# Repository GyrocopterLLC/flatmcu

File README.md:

# flatmcu
Hardware design for the flatmcu - an STM32G4 based BLDC / FOC motor controller.

## Features
All schematic and layout was created with KiCad EDA (https://kicad.org).

The controller is based on the STM32G473CB microcontroller from ST Microelectronics. It contains an ARM Cortex-M4 core at up to 170MHz. The three-phase bridge driver is the TI DRV8353RS, which also contains shunt resistor current sensors and a 95V buck regulator.

The MOSFETs in the three-phase bridge (Toshiba TPW4R50ANH) are dual-side cooling. There's a large metal pad on top of them. A heatsink should be attached there. The opposite side of the board is intended for soldering on the large battery and phase wires.

## Schematic
### Main

### Microcontroller

### Three-phase bridge

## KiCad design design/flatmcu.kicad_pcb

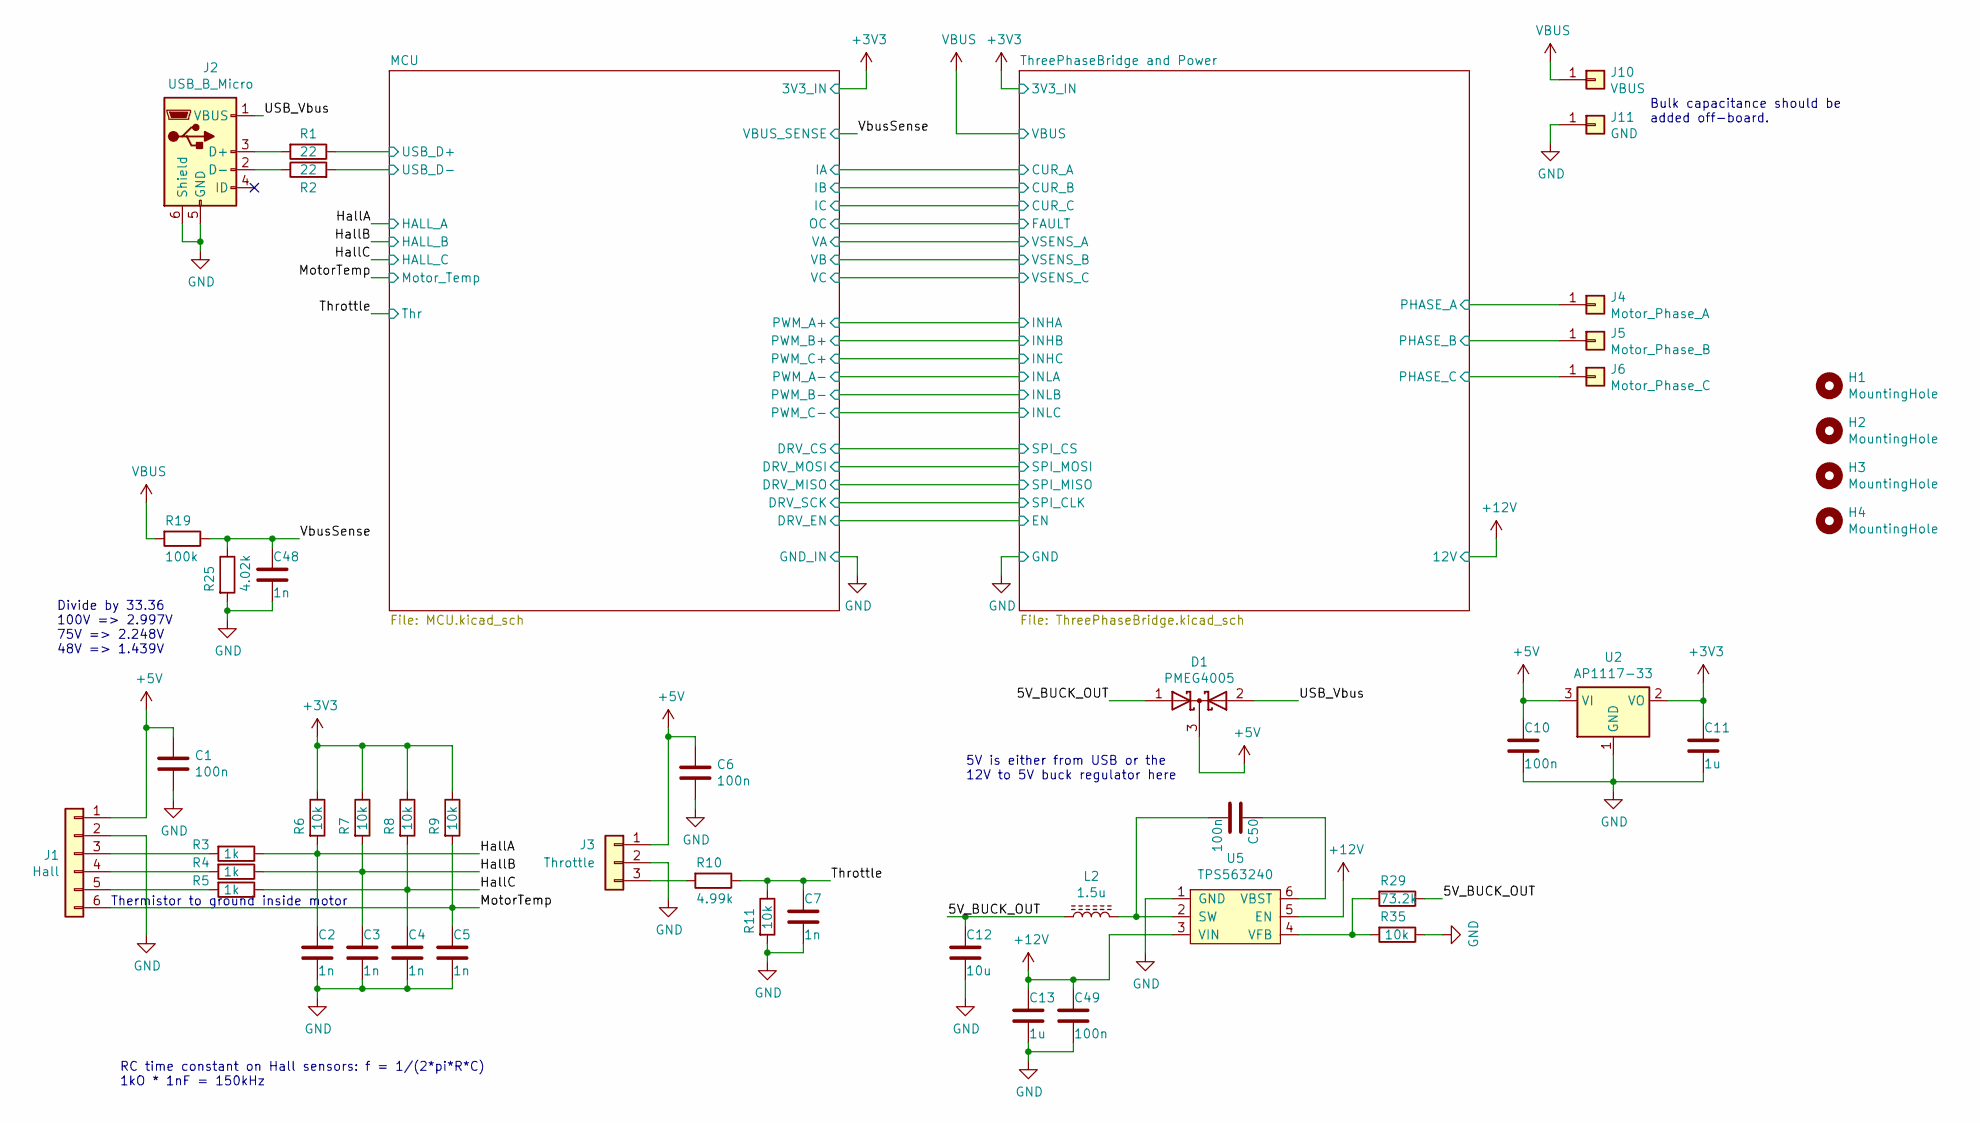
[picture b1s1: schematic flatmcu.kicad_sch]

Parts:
C1, C6, C10: 100n; C_0603_1608Metric; Voltage 6.3V
C2, C3, C4, C5, C7, C48: 1n; C_0603_1608Metric; Voltage 6.3V
C11: 1u; C_0603_1608Metric; Voltage 6.3V
C12: 10u; C_0603_1608Metric; Voltage 6.3V
C13: 1u; C_0603_1608Metric; Voltage 16V
C49, C50: 100n; C_0603_1608Metric; Voltage 16V
D1: PMEG4005; SOT-23
H1, H2, H3, H4: MountingHole; MountingHole_3.2mm_M3
J1: Hall; JST_XH_B6B-XH-A_1x06_P2.50mm_Vertical
J2: USB_B_Micro; USB_Micro_B_Female_10118193-0001LF
J3: Throttle; JST_XH_B3B-XH-A_1x03_P2.50mm_Vertical
J4: Motor_Phase_A; SolderWirePad_1x01_SMD_5x10mm
J5: Motor_Phase_B; SolderWirePad_1x01_SMD_5x10mm
J6: Motor_Phase_C; SolderWirePad_1x01_SMD_5x10mm
J10: VBUS; SolderWirePad_1x01_SMD_5x10mm
J11: GND; SolderWirePad_1x01_SMD_5x10mm
L2: 1.5u; Bourns_SRN3015
R1, R2: 22; R_0603_1608Metric
R3, R4, R5: 1k; R_0603_1608Metric
R6, R7, R8, R9, R11, R35: 10k; R_0603_1608Metric
R10: 4.99k; R_0603_1608Metric
R19: 100k; R_0603_1608Metric
R25: 4.02k; R_0603_1608Metric
R29: 73.2k; R_0603_1608Metric
U2: AP1117-33; SOT-223-3_TabPin2
U5: TPS563240; SOT-23-6

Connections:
+3V3: C11.1, R6.1, R7.1, R8.1, R9.1, U2.2 (VO); also elsewhere on the board
+5V: C1.1, C6.1, C10.1, D1.3 (K), J1.1, J3.1, U2.3 (VI)
+12V: C13.1, C49.1, U5.3 (VIN), U5.5 (EN); also elsewhere on the board
/5V_BUCK_OUT: C12.1, D1.1 (A), L2.1, R29.1
/HallA: C2.1, R3.1, R6.2; also elsewhere on the board
/HallB: C3.1, R4.1, R7.2; also elsewhere on the board
/HallC: C4.1, R5.1, R8.2; also elsewhere on the board
/MCU/USB_D+: R1.1; also elsewhere on the board
/MCU/USB_D-: R2.2; also elsewhere on the board
/MotorTemp: C5.1, J1.6, R9.2; also elsewhere on the board
/ThreePhaseBridge and Power/PHASE_A: J4.1; also elsewhere on the board
/ThreePhaseBridge and Power/PHASE_B: J5.1; also elsewhere on the board
/ThreePhaseBridge and Power/PHASE_C: J6.1; also elsewhere on the board
/Throttle: C7.1, R10.1, R11.1; also elsewhere on the board
/USB_Vbus: D1.2 (A), J2.1 (VBUS)
/VbusSense: C48.1, R19.1, R25.1; also elsewhere on the board
GND: C1.2, C2.2, C3.2, C4.2, C5.2, C6.2, C7.2, C10.2, C11.2, C12.2, C13.2, C48.2, C49.2, J1.2, J2.5 (GND), J2.6 (Shield), J3.2, J11.1, R11.2, R25.2, R35.1, U2.1 (GND), U5.1 (GND); also elsewhere on the board
unnamed: C50.1, U5.6 (VBST)
unnamed: C50.2, L2.2, U5.2 (SW)
unnamed: J1.3, R3.2
unnamed: J1.4, R4.2
unnamed: J1.5, R5.2
unnamed: J2.2 (D-), R2.1
unnamed: J2.3 (D+), R1.2
unnamed: J3.3, R10.2
unnamed: R29.2, R35.2, U5.4 (VFB)
VBUS: J10.1, R19.2; also elsewhere on the board

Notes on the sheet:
RC time constant on Hall sensors: f = 1/(2*pi*R*C) 1kO * 1nF = 150kHz
Divide by 33.36 100V => 2.997V 75V => 2.248V 48V => 1.439V
Thermistor to ground inside motor
Bulk capacitance should be added off-board.
5V is either from USB or the 12V to 5V buck regulator here

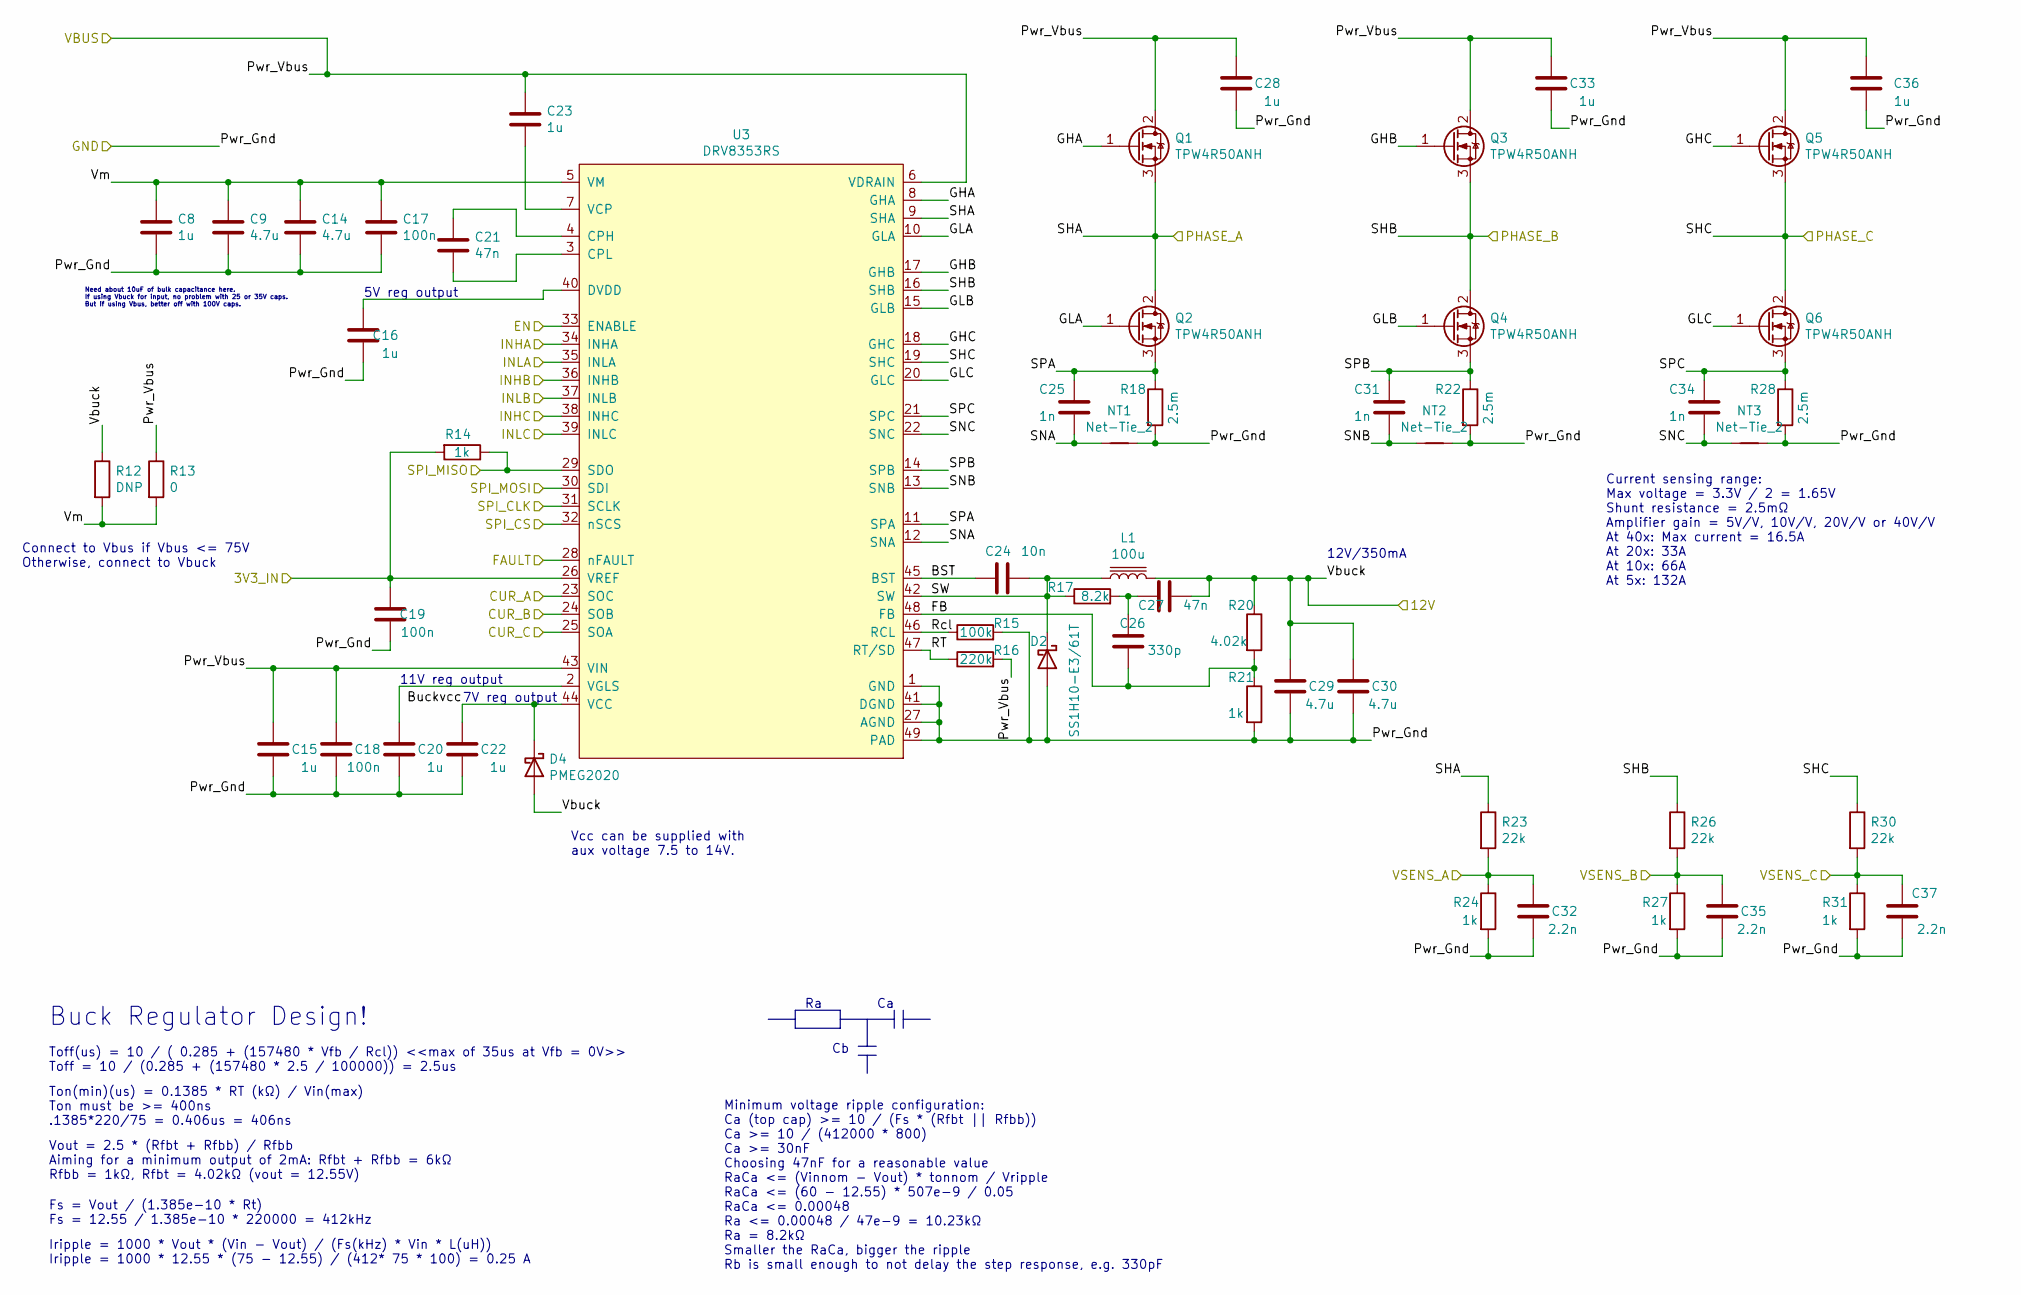
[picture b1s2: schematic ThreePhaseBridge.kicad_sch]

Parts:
C8: 1u; C_1210_3225Metric; Voltage 100V
C9, C14: 4.7u; C_1210_3225Metric; Voltage 100V
C15, C28, C33, C36: 1u; C_1206_3216Metric; Voltage 100V
C16: 1u; C_0603_1608Metric; Voltage 6.3V
C17, C18: 100n; C_0805_2012Metric; Voltage 100V
C19: 100n; C_0603_1608Metric; Voltage 6.3V
C20, C22, C23: 1u; C_0603_1608Metric; Voltage 16V
C21: 47n; C_0805_2012Metric; Voltage 100V
C24: 10n; C_0603_1608Metric; Voltage 16V
C25, C31, C34: 1n; C_0603_1608Metric
C26: 330p; C_0603_1608Metric; Voltage 16V
C27: 47n; C_0603_1608Metric; Voltage 16V
C29, C30: 4.7u; C_0805_2012Metric; Voltage 16V
C32, C35, C37: 2.2n; C_0603_1608Metric; Voltage 16V
D2: SS1H10-E3/61T; D_SMA
D4: PMEG2020; D_SOD-323F
L1: 100u; NR6045
NT1, NT2, NT3: Net-Tie_2; NetTie-2_SMD_Pad0.5mm
Q1, Q2, Q3, Q4, Q5, Q6: TPW4R50ANH; Toshiba_DSOP-Advance
R12: DNP; R_0603_1608Metric
R13: 0; R_0603_1608Metric
R14, R21, R24, R27, R31: 1k; R_0603_1608Metric
R15: 100k; R_0603_1608Metric
R16: 220k; R_0603_1608Metric
R17: 8.2k; R_0603_1608Metric
R18, R22, R28: 2.5m; R_2512_6332Metric
R20: 4.02k; R_0603_1608Metric
R23, R26, R30: 22k; R_0603_1608Metric
U3: DRV8353RS; TI-RGZ-48-QFN

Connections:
+3V3: C19.2, R14.2, U3.26 (VREF); also elsewhere on the board
+12V: C27.1, C29.2, C30.2, D4.2 (A), L1.2, R12.1, R20.1; also elsewhere on the board
/MCU/DRV_CS: U3.32 (nSCS); also elsewhere on the board
/MCU/DRV_EN: U3.33 (ENABLE); also elsewhere on the board
/MCU/DRV_MISO: R14.1, U3.29 (SDO); also elsewhere on the board
/MCU/DRV_MOSI: U3.30 (SDI); also elsewhere on the board
/MCU/DRV_SCK: U3.31 (SCLK); also elsewhere on the board
/MCU/VA: C32.2, R23.2, R24.1; also elsewhere on the board
/MCU/VB: C35.2, R26.2, R27.1; also elsewhere on the board
/MCU/VC: C37.2, R30.2, R31.1; also elsewhere on the board
/ThreePhaseBridge and Power/BST: C24.2, U3.45 (BST)
/ThreePhaseBridge and Power/Buckvcc: C22.2, D4.1 (K), U3.44 (VCC)
/ThreePhaseBridge and Power/CUR_A: U3.23 (SOC); also elsewhere on the board
/ThreePhaseBridge and Power/CUR_B: U3.24 (SOB); also elsewhere on the board
/ThreePhaseBridge and Power/CUR_C: U3.25 (SOA); also elsewhere on the board
/ThreePhaseBridge and Power/FAULT: U3.28 (nFAULT); also elsewhere on the board
/ThreePhaseBridge and Power/FB: C26.1, R20.2, R21.1, U3.48 (FB)
/ThreePhaseBridge and Power/GHA: Q1.1 (G), U3.8 (GHA)
/ThreePhaseBridge and Power/GHB: Q3.1 (G), U3.17 (GHB)
/ThreePhaseBridge and Power/GHC: Q5.1 (G), U3.18 (GHC)
/ThreePhaseBridge and Power/GLA: Q2.1 (G), U3.10 (GLA)
/ThreePhaseBridge and Power/GLB: Q4.1 (G), U3.15 (GLB)
/ThreePhaseBridge and Power/GLC: Q6.1 (G), U3.20 (GLC)
/ThreePhaseBridge and Power/INHA: U3.34 (INHA); also elsewhere on the board
/ThreePhaseBridge and Power/INHB: U3.36 (INHB); also elsewhere on the board
/ThreePhaseBridge and Power/INHC: U3.38 (INHC); also elsewhere on the board
/ThreePhaseBridge and Power/INLA: U3.35 (INLA); also elsewhere on the board
/ThreePhaseBridge and Power/INLB: U3.37 (INLB); also elsewhere on the board
/ThreePhaseBridge and Power/INLC: U3.39 (INLC); also elsewhere on the board
/ThreePhaseBridge and Power/PHASE_A: Q1.3 (S), Q2.2 (D), R23.1, U3.9 (SHA); also elsewhere on the board
/ThreePhaseBridge and Power/PHASE_B: Q3.3 (S), Q4.2 (D), R26.1, U3.16 (SHB); also elsewhere on the board
/ThreePhaseBridge and Power/PHASE_C: Q5.3 (S), Q6.2 (D), R30.1, U3.19 (SHC); also elsewhere on the board
/ThreePhaseBridge and Power/RT: R16.1, U3.47 (RT/SD)
/ThreePhaseBridge and Power/Rcl: R15.1, U3.46 (RCL)
/ThreePhaseBridge and Power/SNA: C25.1, NT1.1, U3.12 (SNA)
/ThreePhaseBridge and Power/SNB: C31.1, NT2.1, U3.13 (SNB)
/ThreePhaseBridge and Power/SNC: C34.1, NT3.1, U3.22 (SNC)
/ThreePhaseBridge and Power/SPA: C25.2, Q2.3 (S), R18.1, U3.11 (SPA)
/ThreePhaseBridge and Power/SPB: C31.2, Q4.3 (S), R22.1, U3.14 (SPB)
/ThreePhaseBridge and Power/SPC: C34.2, Q6.3 (S), R28.1, U3.21 (SPC)
/ThreePhaseBridge and Power/SW: C24.1, D2.1 (K), L1.1, R17.1, U3.42 (SW)
/ThreePhaseBridge and Power/Vm: C8.1, C9.1, C14.1, C17.1, R12.2, R13.2, U3.5 (VM)
GND: C8.2, C9.2, C14.2, C15.1, C16.1, C17.2, C18.1, C19.1, C20.1, C22.1, C28.1, C29.1, C30.1, C32.1, C33.1, C35.1, C36.1, C37.1, D2.2 (A), NT1.2, NT2.2, NT3.2, R15.2, R18.2, R21.2, R22.2, R24.2, R27.2, R28.2, R31.2, U3.1 (GND), U3.27 (AGND), U3.41 (DGND), U3.49 (PAD); also elsewhere on the board
unnamed: C16.2, U3.40 (DVDD)
unnamed: C20.2, U3.2 (VGLS)
unnamed: C21.1, U3.4 (CPH)
unnamed: C21.2, U3.3 (CPL)
unnamed: C23.2, U3.7 (VCP)
unnamed: C26.2, C27.2, R17.2
VBUS: C15.2, C18.2, C23.1, C28.2, C33.2, C36.2, Q1.2 (D), Q3.2 (D), Q5.2 (D), R13.1, R16.2, U3.6 (VDRAIN), U3.43 (VIN); also elsewhere on the board

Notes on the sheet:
Buck Regulator Design!
Current sensing range: Max voltage = 3.3V / 2 = 1.65V Shunt resistance = 2.5mΩ Amplifier gain = 5V/V, 10V/V, 20V/V or 40V/V At 40x: Max current = 16.5A At 20x: 33A At 10x: 66A At 5x: 132A
Vout = 2.5 * (Rfbt + Rfbb) / Rfbb Aiming for a minimum output of 2mA: Rfbt + Rfbb = 6kΩ Rfbb = 1kΩ, Rfbt = 4.02kΩ (vout = 12.55V)
5V reg output
Vcc can be supplied with aux voltage 7.5 to 14V.
Minimum voltage ripple configuration: Ca (top cap) >= 10 / (Fs * (Rfbt || Rfbb)) Ca >= 10 / (412000 * 800) Ca >= 30nF Choosing 47nF for a reasonable value RaCa <= (Vinnom - Vout) * tonnom / Vripple RaCa <= (60 - 12.55) * 507e-9 / 0.05 RaCa <= 0.00048 Ra <= 0.00048 / 47e-9 = 10.23kΩ Ra = 8.2kΩ Small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
12V/350mA
11V reg output
Iripple = 1000 * Vout * (Vin - Vout) / (Fs(kHz) * Vin * L(uH)) Iripple = 1000 * 12.55 * (75 - 12.55) / (412* 75 * 100) = 0.25 A
Ton(min)(us) = 0.1385‬ * RT (kΩ) / Vin(max) Ton must be >= 400ns .1385*220/75 = 0.406us = 406ns
7V reg output
Connect to Vbus if Vbus <= 75V Otherwise, connect to Vbuck
Fs = Vout / (1.385e-10 * Rt) Fs = 12.55 / 1.385e-10 * 220000 = 412kHz
Toff(us) = 10 / ( 0.285 + (157480 * Vfb / Rcl)) <<max of 35us at Vfb = 0V>> Toff = 10 / (0.285 + (157480 * 2.5 / 100000)) = 2.5us
Need about 10uF of bulk capacitance here. If using Vbuck for input, no problem with 25 or 35V caps. But if using Vbus, better off with 100V caps.

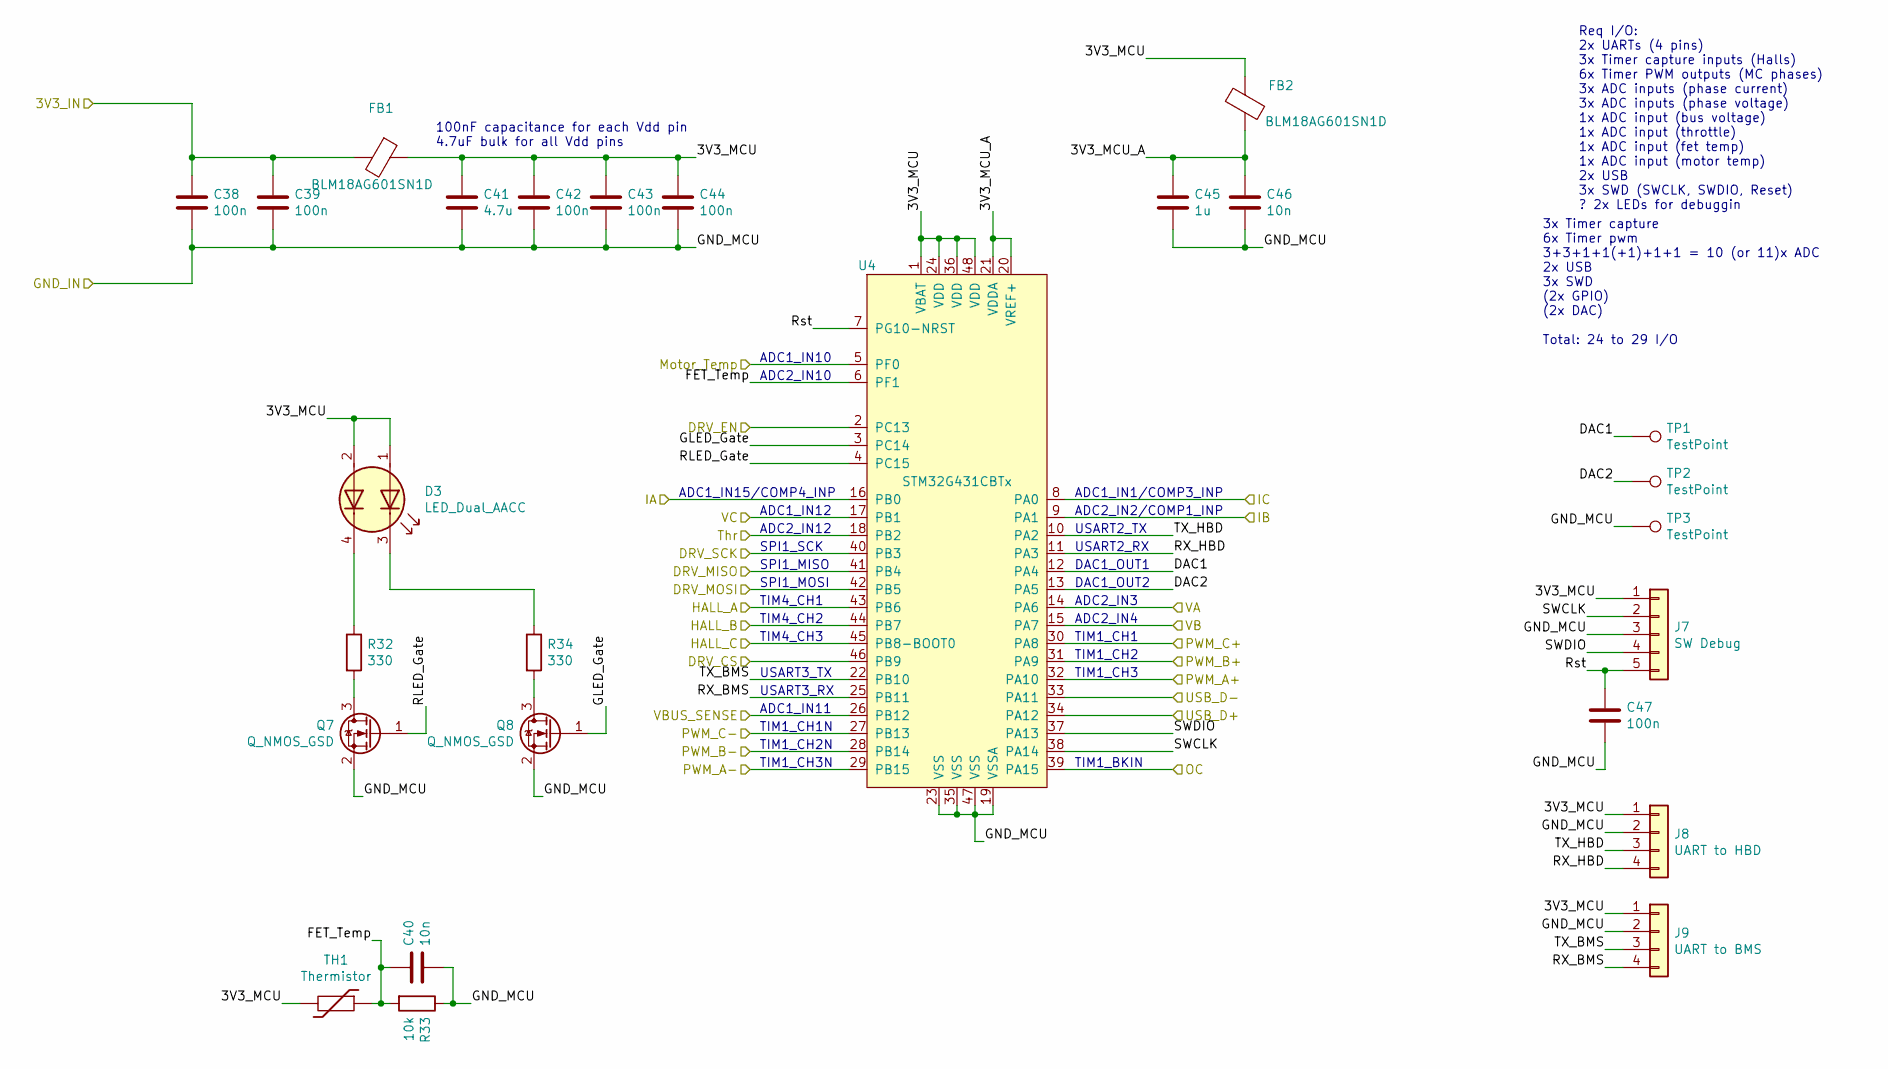
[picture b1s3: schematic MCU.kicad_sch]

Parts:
C38, C39, C42, C43, C44, C47: 100n; C_0603_1608Metric
C40, C46: 10n; C_0603_1608Metric
C41: 4.7u; C_0603_1608Metric
C45: 1u; C_0603_1608Metric
D3: LED_Dual_AACC; LED_RGB_1210
FB1, FB2: BLM18AG601SN1D; R_0603_1608Metric
J7: SW Debug; JST_SH_SM05B-SRSS-TB_1x05-1MP_P1.00mm_Horizontal
J8: UART to HBD; JST_XH_B4B-XH-A_1x04_P2.50mm_Vertical
J9: UART to BMS; JST_XH_B4B-XH-A_1x04_P2.50mm_Vertical
Q7, Q8: Q_NMOS_GSD; SOT-23
R32, R34: 330; R_0603_1608Metric
R33: 10k; R_0603_1608Metric
TH1: Thermistor; R_0603_1608Metric
TP1, TP2, TP3: TestPoint; PinHeader_1x01_P1.00mm_Vertical
U4: STM32G431CBTx; LQFP-48_7x7mm_P0.5mm

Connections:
+3V3: C38.1, C39.1, FB1.2; also elsewhere on the board
/HallA: U4.43 (PB6); also elsewhere on the board
/HallB: U4.44 (PB7); also elsewhere on the board
/HallC: U4.45 (PB8-BOOT0); also elsewhere on the board
/MCU/3V3_MCU: C41.1, C42.1, C43.1, C44.1, D3.1 (A1), D3.2 (A2), FB1.1, FB2.2, J7.1, J8.1, J9.1, TH1.2, U4.1 (VBAT), U4.24 (VDD), U4.36 (VDD), U4.48 (VDD)
/MCU/3V3_MCU_A: C45.1, C46.1, FB2.1, U4.20 (VREF+), U4.21 (VDDA)
/MCU/DAC1: TP1.1, U4.12 (PA4)
/MCU/DAC2: TP2.1, U4.13 (PA5)
/MCU/DRV_CS: U4.46 (PB9); also elsewhere on the board
/MCU/DRV_EN: U4.2 (PC13); also elsewhere on the board
/MCU/DRV_MISO: U4.41 (PB4); also elsewhere on the board
/MCU/DRV_MOSI: U4.42 (PB5); also elsewhere on the board
/MCU/DRV_SCK: U4.40 (PB3); also elsewhere on the board
/MCU/FET_Temp: C40.1, R33.2, TH1.1, U4.6 (PF1)
/MCU/GLED_Gate: Q8.1 (G), U4.3 (PC14)
/MCU/RLED_Gate: Q7.1 (G), U4.4 (PC15)
/MCU/RX_BMS: J9.4, U4.25 (PB11)
/MCU/RX_HBD: J8.4, U4.11 (PA3)
/MCU/Rst: C47.1, J7.5, U4.7 (PG10-NRST)
/MCU/SWCLK: J7.2, U4.38 (PA14)
/MCU/SWDIO: J7.4, U4.37 (PA13)
/MCU/TX_BMS: J9.3, U4.22 (PB10)
/MCU/TX_HBD: J8.3, U4.10 (PA2)
/MCU/USB_D+: U4.34 (PA12); also elsewhere on the board
/MCU/USB_D-: U4.33 (PA11); also elsewhere on the board
/MCU/VA: U4.14 (PA6); also elsewhere on the board
/MCU/VB: U4.15 (PA7); also elsewhere on the board
/MCU/VC: U4.17 (PB1); also elsewhere on the board
/MotorTemp: U4.5 (PF0); also elsewhere on the board
/ThreePhaseBridge and Power/CUR_A: U4.16 (PB0); also elsewhere on the board
/ThreePhaseBridge and Power/CUR_B: U4.9 (PA1); also elsewhere on the board
/ThreePhaseBridge and Power/CUR_C: U4.8 (PA0); also elsewhere on the board
/ThreePhaseBridge and Power/FAULT: U4.39 (PA15); also elsewhere on the board
/ThreePhaseBridge and Power/INHA: U4.32 (PA10); also elsewhere on the board
/ThreePhaseBridge and Power/INHB: U4.31 (PA9); also elsewhere on the board
/ThreePhaseBridge and Power/INHC: U4.30 (PA8); also elsewhere on the board
/ThreePhaseBridge and Power/INLA: U4.29 (PB15); also elsewhere on the board
/ThreePhaseBridge and Power/INLB: U4.28 (PB14); also elsewhere on the board
/ThreePhaseBridge and Power/INLC: U4.27 (PB13); also elsewhere on the board
/Throttle: U4.18 (PB2); also elsewhere on the board
/VbusSense: U4.26 (PB12); also elsewhere on the board
GND: C38.2, C39.2, C40.2, C41.2, C42.2, C43.2, C44.2, C45.2, C46.2, C47.2, J7.3, J8.2, J9.2, Q7.2 (S), Q8.2 (S), R33.1, TP3.1, U4.19 (VSSA), U4.23 (VSS), U4.35 (VSS), U4.47 (VSS); also elsewhere on the board
unnamed: D3.3 (K1), R34.1
unnamed: D3.4 (K2), R32.1
unnamed: Q7.3 (D), R32.2
unnamed: Q8.3 (D), R34.2

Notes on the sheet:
ADC1_IN11
TIM1_CH3N
Req I/O: 2x UARTs (4 pins) 3x Timer capture inputs (Halls) 6x Timer PWM outputs (MC phases) 3x ADC inputs (phase current) 3x ADC inputs (phase voltage) 1x ADC input (bus voltage) 1x ADC input (throttle) 1x ADC input (fet temp) 1x ADC input (motor temp) 2x USB 3x SWD (SWCLK, SWDIO, Reset) ? 2x LEDs 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
DAC1_OUT2
TIM4_CH2
USART3_RX
SPI1_MOSI
ADC1_IN10
DAC1_OUT1
ADC2_IN3
ADC2_IN4
TIM1_CH2
SPI1_SCK
TIM1_CH2N
ADC2_IN12
ADC1_IN1/COMP3_INP
TIM4_CH3
100nF capacitance for each Vdd pin 4.7uF bulk for all Vdd pins
USART2_TX
ADC1_IN15/COMP4_INP
TIM4_CH1
TIM1_CH3
USART3_TX
ADC1_IN12
TIM1_CH1N
3x Timer capture 6x Timer pwm 3+3+1+1(+1)+1+1 = 10 (or 11)x ADC 2x USB 3x SWD (2x GPIO) (2x DAC) Total: 24 to 29 I/O
ADC2_IN2/COMP1_INP
TIM1_CH1
USART2_RX
SPI1_MISO
TIM1_BKIN
ADC2_IN10

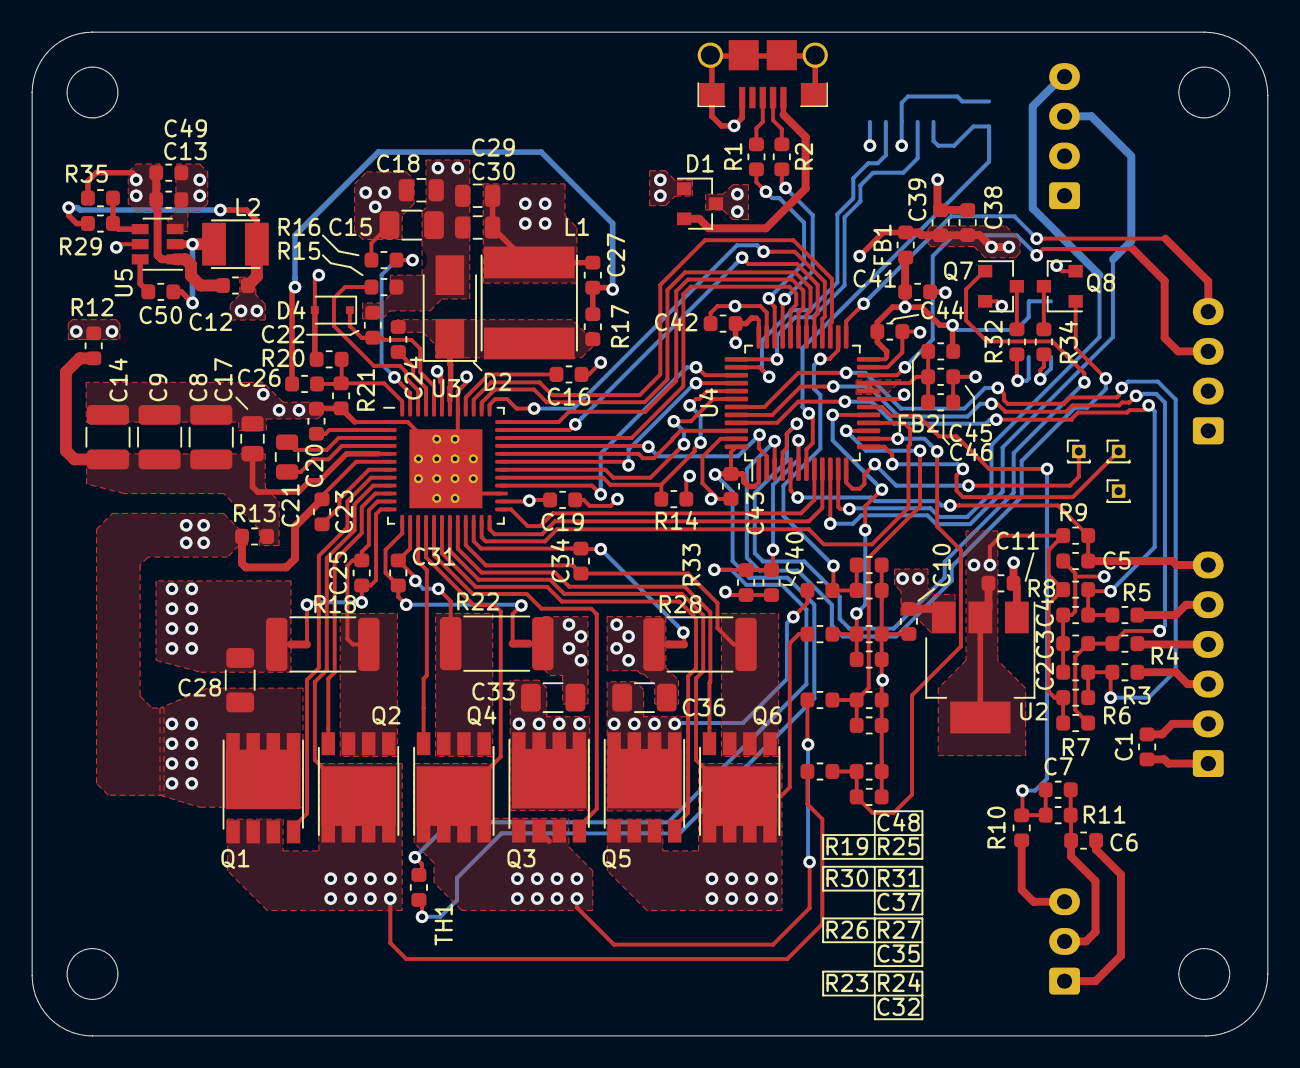
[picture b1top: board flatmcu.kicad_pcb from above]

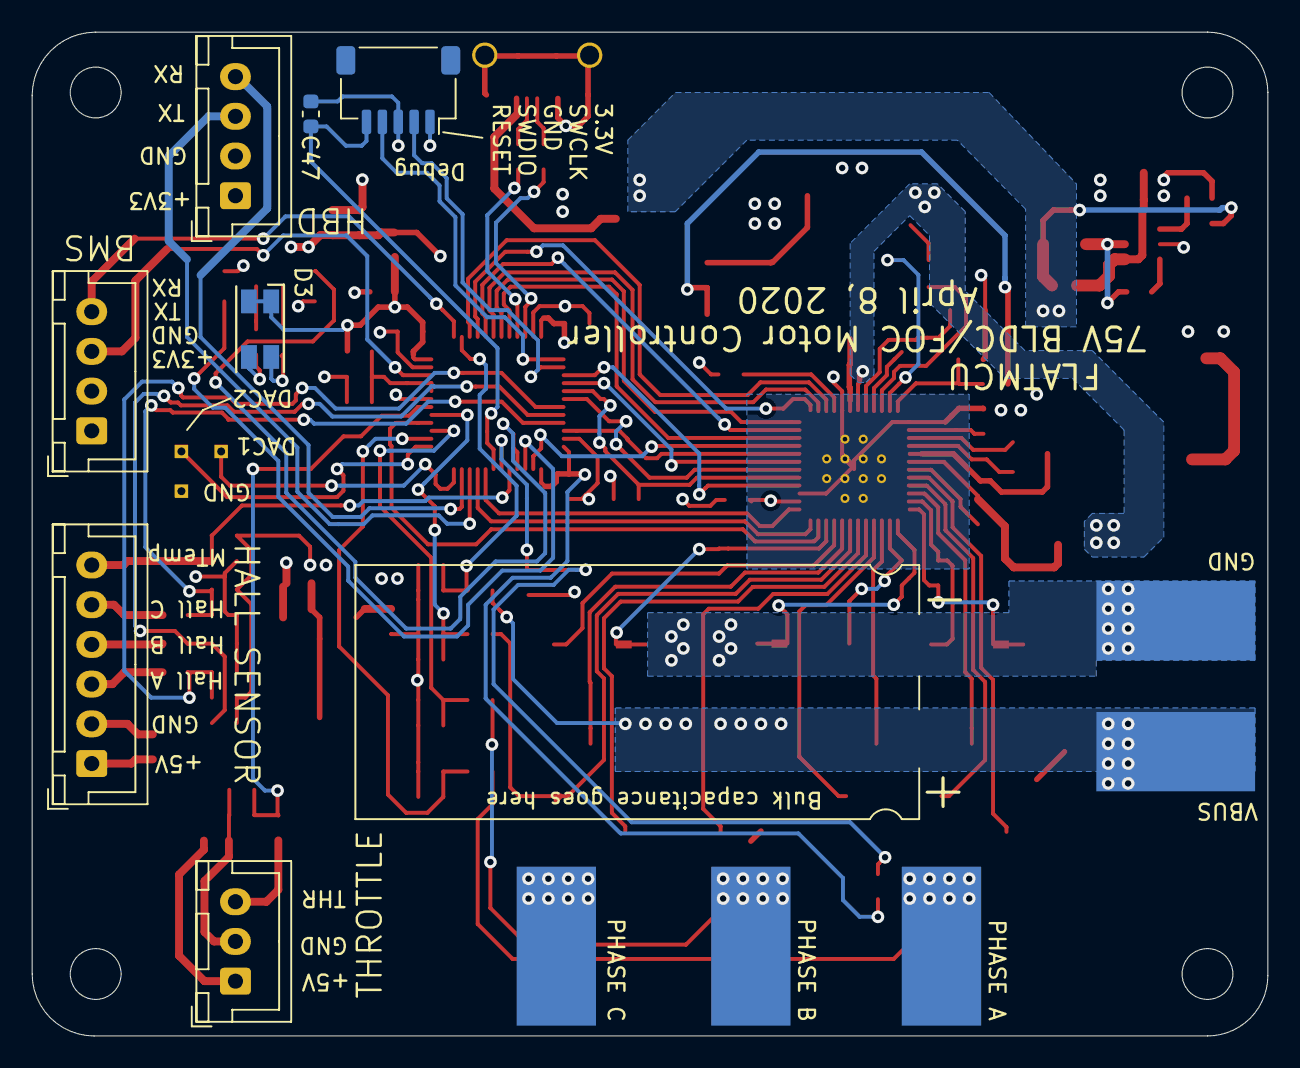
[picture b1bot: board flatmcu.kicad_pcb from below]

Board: 4 copper layers, 77.8 x 63.2 mm, 127 parts (12 on the bottom side), 88 nets.

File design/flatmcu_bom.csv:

*** Bill of Materials ***,,,,
* Note: Many of the resistors and capacitors do not have specific part numbers listed. Substitute with any that meet the value / footprint / voltage specs. *,,,,
* Suggest to use X5R/X7R capacitors or better. *,,,,
,,,,
Part No,Value,Footprint,Qty,Refs
???,100n/100V,C0805,2,"C17, C18"
CL10A104KA8NNNC,100n/25V,C0603,11,"C1,C10,C19,C38, C42, C43, C44, C47, C49, C50, C6"
???,1u/16V,C0603,8,"C11, C13, C16, C20, C22, C23, C39, C45"
???,10n/50V,C0603,3,"C24, C40, C46"
CRM188R61A106KE69D,10u/10V,C0603,1,C12
???,1n/50V,C0603,9,"C2, C3, C4, C5, C7, C25, C31, C34, C48"
GCM21BC72A105KE36L,1u/100V,C0805,5,"C8, C15, C28, C33, C36"
???,2.2n/50V,C0603,3,"C32, C35, C37"
???,330p/50V,C0603,1,C26
???,4.7u/6.3V,C0603,1,C41
???,4.7u/16V,C0805,2,"C29, C30"
GCM32DC72A475KE02L,4.7u/100V,C1210,2,"C9, C14"
???,47n/16V,C0603,1,C27
CL21B473KCCWPNC,47n/100V,C0805,1,C21
"PMEG4005CT,215",Dual Schottky 40V 500mA,SOT23,1,D1
SS1H10-E3/61T,Schottky 100V 1A,SMA,1,D2
LTST-C155GEKT,Red/Green LED,4-SMD,1,D3
"PMEG2020EJ,115",Schottky 20V 2A,SOD323F,1,D4
TPW4R50ANH,N-CH 100V 92A,8DSOP,6,"Q1, Q2, Q3, Q4, Q5, Q6"
AO3400A,N-CH 30V 6.7A,SOT23,2,"Q7, Q8"
NR6045T101M,100uH 800mA,6x6mm,1,L1
SRN3015-1R5Y,1.5uH 2.1A,3x3mm,1,L2
BLM18AG601SN1D,Ferrite Bead 600ohm,R0603,2,"FB1, FB2"
???,0R,R0603,1,R13
???,33R,R0603,2,"R1, R2"
???,330R,R0603,2,"R32, R34"
???,100k,R0603,2,"R15, R19"
???,10k,R0603,7,"R6, R7, R8, R9, R11, R33, R35"
???,1k,R0603,8,"R3, R4, R5, R14, R21, R24, R27, R31"
ERJ-M1WTF2M0U,0R002,R2512,3,"R18, R22, R28"
ERJ-3EKF2203V,220k,R0603,1,R16
???,22k,R0603,3,"R23, R26, R30"
???,4.02k,R0603,2,"R20, R25"
???,4.99k,R0603,1,R10
???,73.2k,R0603,1,R29
???,8.2k,R0603,1,R17
ERT-J1VR103J,NTC Thermistor 10k,R0603,1,TH1
B5B-XH-A(LF)(SN),5 pin JST XH,B5B-XH-A(LF)(SN),1,J1
10118193-0001LF,USB Micro B THT,10118193-0001LF,1,J2
B3B-XH-A(LF)(SN),3 pin JST XH,B3B-XH-A(LF)(SN),1,J3
BM05B-SRSS-TB(LF)(SN),5 pin JST SR,BM05B-SRSS-TB(LF)(SN),1,J7
B4B-XH-A(LF)(SN),4 pin JST XH,B4B-XH-A(LF)(SN),2,"J8, J9"
AP1117E33G-13,LDO 18Vin 3.3Vout 1.1A,SOT223,1,U2
DRV8353RSRGZT,Three phase driver,48QFN,1,U3
STM32G473CET6,MCU Arm Cortex-M4,48LQFP,1,U4
TPS563240DDCT,Buck Reg Adj 3A 17Vin,SOT23-6,1,U5

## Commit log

2020-05-01 Initial import
2020-05-01 Updated readme.
2020-05-03 New 3D renders
2021-11-08 Update README.md
    https://forum.kicad.info/t/warning-avoid-all-links-to-kicad-pcb-org-use-kicad-org/31521
2022-09-16 Updated README.md - corrected link to kicad site
2023-11-07 updated for kicad 7
2023-11-07 updated 3d model path
